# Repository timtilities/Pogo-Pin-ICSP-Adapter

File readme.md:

Pogo pin ICSP programming adapter

***

The standard 2x3 ICSP header that is usually used for Arduino/Atmel projects is bulky and requires a wide header on the PCB. For decent sized through-hole projects this may be OK, but I do a lot of SMD boards (much easier since you don't have to drill a bunch of holes).  I found lots of different ideas on the web, and decided to use pogo pins.  In addition, I found a great project that didn't require multiple PCBs to stabilize the pogo pins! Unfortunately, I don't remember who's project that was so I can't give them credit. Just keep in mind this idea was not entirely mine, nor is it unique. That being said, here are a couple pics of the raw PCB and the finished products:

There are 2 versions, the first being a "normal" sized board with a pitch of about 1.83mm, the second being a tiny version with a pitch of about 1.27mm. In most cases, I go with the 1.83 pitch board since I can route small traces between the pads. The 1.27mm version is good for those boards with no room to spare, but I have never needed it. The Kicad library only includes the larger 1.83mm pitch footprint. 

Here's an example of using the ICSP pads designed for these pogo adapters:

To assemble the adapter, carefully solder the pogo pins in between the long PCB traces on the board. If done correctly, they should sit right in between the traces and be fairly stable while you solder.  I made the 2 pins on either end slightly longer than the middle pins, but it isn't really necessary.

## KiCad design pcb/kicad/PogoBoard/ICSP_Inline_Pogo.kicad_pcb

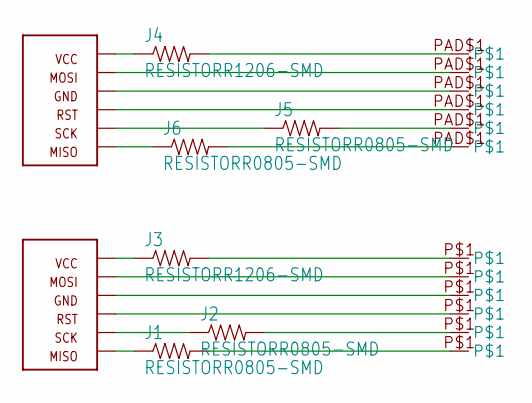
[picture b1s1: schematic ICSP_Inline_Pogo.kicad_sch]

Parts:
GND0: POGO_PADR50; P50_POGO_PIN
GND1: POGO_PADR75; P75_POGO_PIN
J1, J2, J5, J6: RESISTORR0805-SMD; R0805
J3, J4: RESISTORR1206-SMD; R1206
MISO0: POGO_PADR50; P50_POGO_PIN
MISO1: POGO_PADR75; P75_POGO_PIN
MOSI0: POGO_PADR50; P50_POGO_PIN
MOSI1: POGO_PADR75; P75_POGO_PIN
RST0: POGO_PADR50; P50_POGO_PIN
RST1: POGO_PADR75; P75_POGO_PIN
SCK0: POGO_PADR50; P50_POGO_PIN
SCK1: POGO_PADR75; P75_POGO_PIN
U$1, U$3: AVR_ICSP_6P2X3_THP; AVR_ICSP_2X3_THP
VCC0: POGO_PADR50; P50_POGO_PIN
VCC1: POGO_PADR75; P75_POGO_PIN

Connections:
GND: GND0.P$1, U$3.GND
GND1: GND1.PAD$1, U$1.GND
MISO: J1.1, U$3.MISO
MISO1: J6.2, MISO1.PAD$1
MOSI: MOSI0.P$1, U$3.MOSI
MOSI1: MOSI1.PAD$1, U$1.MOSI
unnamed: J1.2, MISO0.P$1
unnamed: J3.1, U$3.VCC
unnamed: J2.1, U$3.SCK
unnamed: J6.1, U$1.MISO
unnamed: J5.2, SCK1.PAD$1
unnamed: J4.1, U$1.VCC
RST: RST0.P$1, U$3.RST
RST1: RST1.PAD$1, U$1.RST
SCK: J2.2, SCK0.P$1
SCK1: J5.1, U$1.SCK
VCC: J3.2, VCC0.P$1
VCC1: J4.2, VCC1.PAD$1

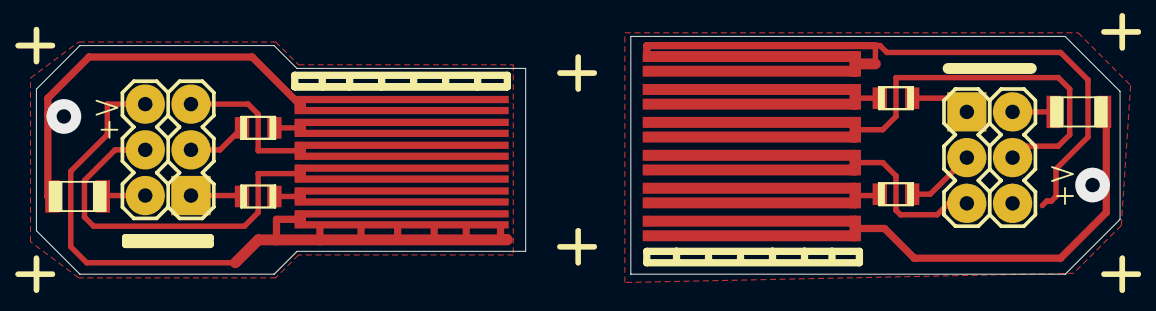
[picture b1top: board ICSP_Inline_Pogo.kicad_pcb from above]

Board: 2 copper layers, 60.2 x 13.2 mm, 20 parts (0 on the bottom side), 18 nets.

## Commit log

2026-03-22 initial
